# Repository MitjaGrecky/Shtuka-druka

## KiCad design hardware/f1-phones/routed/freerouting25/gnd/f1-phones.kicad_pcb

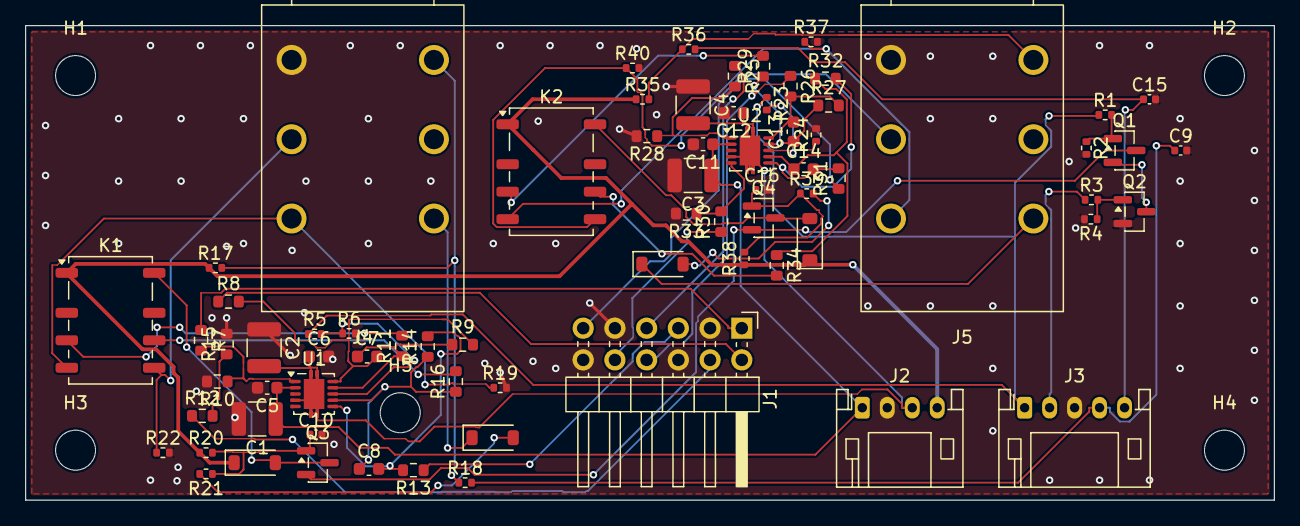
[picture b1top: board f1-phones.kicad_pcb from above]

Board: 2 copper layers, 100.0 x 38.0 mm, 78 parts (0 on the bottom side), 52 nets.

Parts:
C1, C2, C3, C4: 10u 25V; C_1210_3225Metric
C5, C6, C11, C12: 100n 25V; C_0603_1608Metric
C7, C8, C13, C14: 22p C0G; C_0603_1608Metric
C9, C10, C15, C16: 100n; C_0402_1005Metric
D1, D3: B5819W; D_SOD-123
D2, D4: 1N4148W; D_SOD-123
H1, H2, H3, H4, H5: M3; MountingHole_3.2mm_M3_ISO7380
J1: from A1; PinHeader_2x06_P2.54mm_Horizontal
J2: from PW; JST_PH_S4B-PH-K_1x04_P2.00mm_Horizontal
J3: from R1 (mute, detect); JST_PH_S5B-PH-K_1x05_P2.00mm_Horizontal
J4: PHONES 1; Jack_6.35mm_Cliff_S1_Horizontal
J5: PHONES 2; Jack_6.35mm_Cliff_S1_Horizontal
K1, K2: G6K-2F-Y 5V; Relay_DPDT_Omron_G6K-2F-Y
Q1, Q2, Q3, Q4: AO3400A; SOT-23
R1, R3, R5, R23: 1k; R_0402_1005Metric
R2, R4, R6, R17, R22, R24, R35, R40: 100k; R_0402_1005Metric
R7, R8, R12, R13, R25, R26, R30, R31: 10k; R_0603_1608Metric
R9, R10, R14, R15, R27, R28, R32, R33: 20k; R_0603_1608Metric
R11, R16, R29, R34: 10; R_0603_1608Metric
R18, R19, R36, R37: 10k; R_0402_1005Metric
R20, R38: 1M; R_0402_1005Metric
R21, R39: 100; R_0402_1005Metric
U1, U2: OPA1622; Texas_S-PVSON-N10

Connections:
+5V: D2.1, D4.1, J2.4, K1.A1, K2.A1, R17.1, R20.1, R35.1, R38.1
/+12V: C1.1, C3.1, C5.1, C11.1, J2.1, U1.2, U2.2
/-12V: C2.2, C4.2, C6.1, C12.1, J2.3, U1.4, U1.11, U2.4, U2.11
/COIL_K: Q1.3, Q3.2, Q4.2
/COIL_KS: Q1.2, Q2.3
/DET_HP1: C9.1, J3.4, R18.2
/DET_HP2: C15.1, J3.5, R36.2
/HP1L_IM: C7.2, R8.2, R9.2, U1.10
/HP1L_IP: R7.2, R10.1, U1.1
/HP1L_N: J1.2, R8.1
/HP1L_O: C7.1, R9.1, R11.1, U1.9
/HP1L_OR: K1.11, R11.2
/HP1L_P: J1.1, R7.1
/HP1R_IM: C8.2, R13.2, R14.2, U1.6
/HP1R_IP: R12.2, R15.1, U1.5
/HP1R_N: J1.5, R13.1
/HP1R_O: C8.1, R14.1, R16.1, U1.7
/HP1R_OR: K1.21, R16.2
/HP1R_P: J1.4, R12.1
/HP1_COIL: D2.2, K1.A2, Q3.3
/HP1_EN: R5.2, R6.1, U1.8
/HP1_G: C10.1, Q3.1, R20.2, R21.1
/HP1_GD: D1.2, R21.2
/HP1_RING: J4.R, K1.24, R22.1
/HP1_SN: J4.SN, R17.2, R18.1
/HP1_TIP: J4.T, K1.14, R19.1
/HP1_TN: D1.1, J4.TN
/HP2L_IM: C13.2, R26.2, R27.2, U2.10
/HP2L_IP: R25.2, R28.1, U2.1
/HP2L_N: J1.8, R26.1
/HP2L_O: C13.1, R27.1, R29.1, U2.9
/HP2L_OR: K2.11, R29.2
/HP2L_P: J1.7, R25.1
/HP2R_IM: C14.2, R31.2, R32.2, U2.6
/HP2R_IP: R30.2, R33.1, U2.5
/HP2R_N: J1.11, R31.1
/HP2R_O: C14.1, R32.1, R34.1, U2.7
/HP2R_OR: K2.21, R34.2
/HP2R_P: J1.10, R30.1
/HP2_COIL: D4.2, K2.A2, Q4.3
/HP2_EN: R23.2, R24.1, U2.8
/HP2_G: C16.1, Q4.1, R38.2, R39.1
/HP2_GD: D3.2, R39.2
/HP2_RING: J5.R, K2.24, R40.1
/HP2_SN: J5.SN, R35.2, R36.1
/HP2_TIP: J5.T, K2.14, R37.1
/HP2_TN: D3.1, J5.TN
/MUTE: J3.1, R1.1, R5.1, R23.1
/MUTE_G: Q1.1, R1.2, R2.1
/R2OK_G: Q2.1, R3.2, R4.1
/R2_OK: J3.2, R3.1
GND: C1.2, C2.1, C3.2, C4.1, C5.2, C6.2, C9.2, C10.2, C11.2, C12.2, C15.2, C16.2, J1.3, J1.6, J1.9, J1.12, J2.2, J3.3, J4.S, J5.S, Q2.2, R2.2, R4.2, R6.2, R10.2, R15.2, R19.2, R22.2, R24.2, R28.2, R33.2, R37.2, R40.2, U1.3, U2.3

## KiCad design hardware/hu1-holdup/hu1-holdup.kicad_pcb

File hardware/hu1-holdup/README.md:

# HU1 - hold-up module for the +-14 V rails (P129, P130)

**Status: rev 0.1 (21.11.2026): schematic and placed board, 2 layers, 35 x 45 mm, ERC 0, DRC 0, parity 0; not routed (UNROUTED rule: 4 capacitors, 2 resistors, 2 diodes, one 3-pin connector).**
Next to PW on a harness <= 80 mm (the place in the enclosure: designer, P130). On a loss of all power the +-14 V rails keep the audio boards alive for >= 6 ms until the output relays have opened (tasks/12, tasks/13 of the team folder).

| Block | Parts | Notes |
|---|---|---|
| Storage | 4 x 470 uF 25 V aluminium electrolytic 10 x 10.5 mm (2 per rail) | 0.94 mF per rail: 4.8 ms at 0.43 A, 7.1 ms at 0.29 A (with the Schottky drop) |
| Inrush limit | 2 x 10 ohm 1206 (one per rail) | LMR33640: soft start 4 ms, low-side limit 3.9-5 A, total output capacitance <= about 1000 uF: 1.4 A peak instead of 3.5 A |
| Discharge path | 2 x SS34 (C8678) | the storage feeds the rail when it sags; drop 0.3-0.4 V |
| Connector | Micro-Fit 3.0 1x3 vertical (43650-0315, latching) | 1 P14, 2 GND, 3 N14; PW has the same connector "to HU1" |

Parts to select (technologist): the 470 uF electrolytic (25 V, 105 C, 10 x 10.5), SS34 availability. License: CERN-OHL-S-2.0 (hardware), AGPL-3.0 (code).

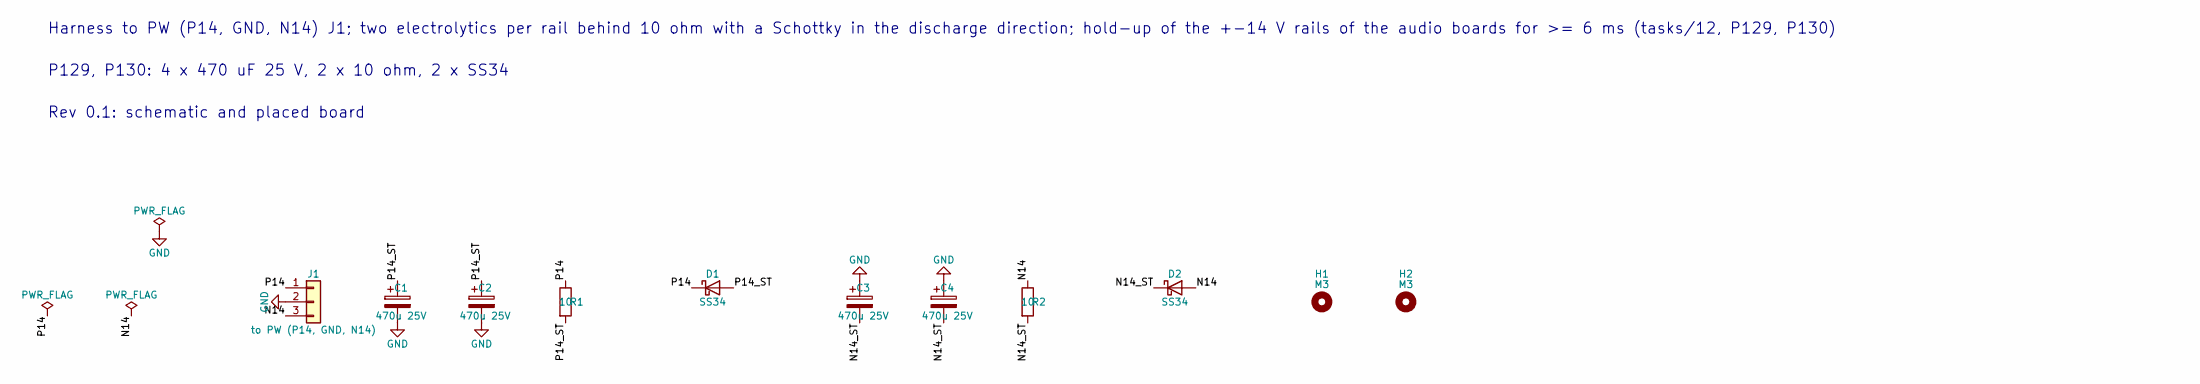
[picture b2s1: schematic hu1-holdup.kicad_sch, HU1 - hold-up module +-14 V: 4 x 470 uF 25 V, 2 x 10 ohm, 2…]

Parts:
C1, C2, C3, C4: 470u 25V; CP_Elec_10x10.5
D1, D2: SS34; D_SMA; LCSC C8678
H1, H2: M3; MountingHole_3.2mm_M3_ISO7380
J1: to PW (P14, GND, N14); Molex_Micro-Fit_3.0_43650-0315_1x03_P3.00mm_Vertical
R1, R2: 10; R_1206_3216Metric

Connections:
/N14: D2.2 (A), J1.3, R2.1
/N14_ST: C3.2, C4.2, D2.1 (K), R2.2
/P14: D1.1 (K), J1.1, R1.1
/P14_ST: C1.1, C2.1, D1.2 (A), R1.2
GND: C1.2, C2.2, C3.1, C4.1, J1.2

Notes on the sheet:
Harness to PW (P14, GND, N14) J1; two electrolytics per rail behind 10 ohm with a Schottky in the discharge direction; hold-up of the +-14 V rails of the audio boards for >= 6 ms (tasks/12, P129, P130)
P129, P130: 4 x 470 uF 25 V, 2 x 10 ohm, 2 x SS34
Rev 0.1: schematic and placed board

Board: 2 copper layers, 11 parts (0 on the bottom side), 5 nets, no tracks yet.

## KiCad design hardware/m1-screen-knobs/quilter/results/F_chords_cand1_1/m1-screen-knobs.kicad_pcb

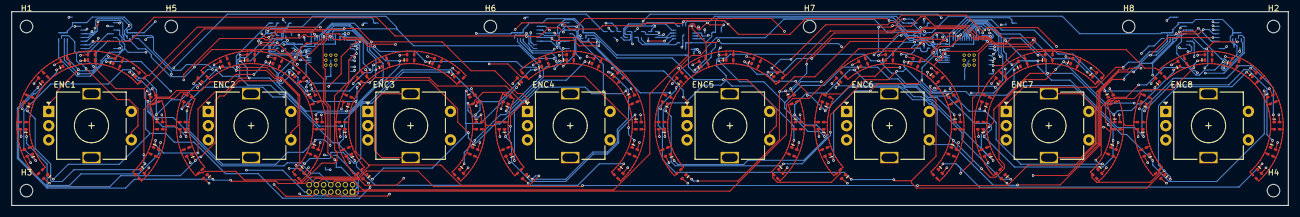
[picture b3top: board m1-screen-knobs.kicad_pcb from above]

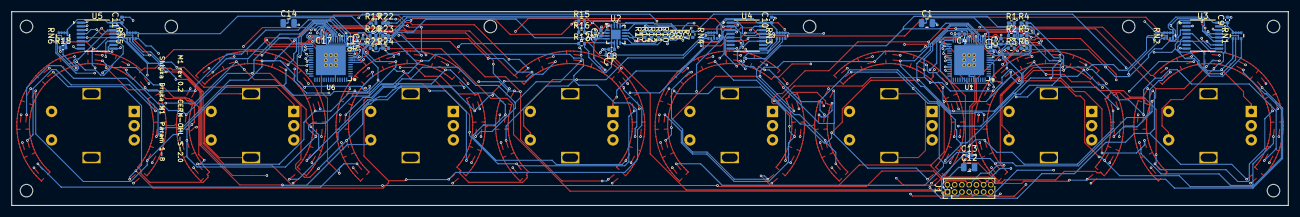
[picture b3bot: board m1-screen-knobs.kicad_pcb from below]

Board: 4 copper layers, 224.0 x 34.0 mm, 174 parts (54 on the bottom side), 114 nets.

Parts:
C1, C14: 4.7u; C_0805_2012Metric
C2, C7, C13, C15: 1u; C_0402_1005Metric
C3, C4, C6, C8, C9, C10, C11, C16, C17: 100n; C_0402_1005Metric
C5: 2.2n; C_0402_1005Metric
C12: 10u; C_0805_2012Metric
D1, D2, D3, D4, D5, D6, D7, D8, D9, D10, D11, D12, D13, D14, D15, D16, D17, D18, D19, D20, D21, D22, D23, D24, D25, D26, D27, D28, D29, D30, D31, D32, D33, D34, D35, D36, D37, D38, D39, D40, D41, D42, D43, D44, D45, D46, D47, D48, D49, D50, D51, D52, D53, D54, D55, D56, D57, D58, D59, D60, D61, D62, D63, D64, D65, D66, D67, D68, D69, D70, D71, D72, D73, D74, D75, D76, D77, D78, D79, D80, D81, D82, D83, D84, D85, D86, D87, D88, D89, D90, D91, D92, D93, D94, D95, D96, D97, D98, D99, D100, D101, D102, D103, D104: XL-1615RGBC-RF; LED_RGB_XL-1615RGBC_1.6x1.5mm
ENC1, ENC2, ENC3, ENC4, ENC5, ENC6, ENC7, ENC8: EC11E smooth, switch; RotaryEncoder_Alps_EC11E-Switch_Vertical_H20mm_Ring
H1, H2, H3, H4, H5, H6, H7, H8: M2; MountingHole_2.2mm_M2
J1: Module bus 2x7 1.27; PinHeader_2x07_P1.27mm_Vertical
R1, R19: 20k 1%; R_0402_1005Metric
R2, R17, R18, R20: 10k; R_0402_1005Metric
R3, R4, R5, R6, R21, R22, R23, R24: 0; R_0402_1005Metric
R7, R8, R9, R10, R11, R12, R13, R14: 560; R_0402_1005Metric
R15, R16: 4.7k; R_0402_1005Metric
RN1, RN2, RN3, RN4, RN5, RN6: 4x10k; R_Array_Convex_4x0402
U1, U6: IS31FL3741A-QFLS4-TR; QFN-60-1EP_7x7mm_P0.4mm_EP5.25x5.25mm
U2: CY8CMBR3108-LQXIT; QFN-16-1EP_3x3mm_P0.5mm_EP1.7x1.7mm
U3, U4, U5: 74HC165PW; TSSOP-16_4.4x5mm_P0.65mm

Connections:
+3V3: C7.1, C8.1, C9.1, C10.1, C11.1, C13.1, J1.5, R2.2, R15.2, R16.2, R17.2, R18.2, R20.2, RN1.5, RN1.6, RN1.7, RN1.8, RN2.5, RN2.6, RN2.7, RN2.8, RN3.5, RN3.6, RN3.7, RN3.8, RN4.5, RN4.6, RN4.7, RN4.8, RN5.5, RN5.6, RN5.7, RN5.8, RN6.5, RN6.6, RN6.7, RN6.8, U2.5, U2.6, U3.16, U4.16, U5.16
+5V: C1.1, C2.1, C3.1, C4.1, C12.1, C14.1, C15.1, C16.1, C17.1, J1.1, J1.2, R6.2, R24.2, U1.14, U1.15, U1.25, U6.14, U6.15, U6.25
A_ADDR: R3.1, R4.1, R5.1, R6.1, U1.8
A_CS1: D1.1, D2.1, D3.1, D4.1, D5.1, D6.1, D7.1, D8.1, D9.1, U1.26
A_CS2: D1.3, D2.3, D3.3, D4.3, D5.3, D6.3, D7.3, D8.3, D9.3, U1.27
A_CS3: D1.4, D2.4, D3.4, D4.4, D5.4, D6.4, D7.4, D8.4, D9.4, U1.28
A_CS4: D18.1, D19.1, D20.1, D21.1, D22.1, D23.1, D24.1, D25.1, D26.1, U1.29
A_CS5: D18.3, D19.3, D20.3, D21.3, D22.3, D23.3, D24.3, D25.3, D26.3, U1.30
A_CS6: D18.4, D19.4, D20.4, D21.4, D22.4, D23.4, D24.4, D25.4, D26.4, U1.31
A_CS7: D10.1, D11.1, D12.1, D13.1, D14.1, D15.1, D16.1, D17.1, U1.32
A_CS8: D10.3, D11.3, D12.3, D13.3, D14.3, D15.3, D16.3, D17.3, U1.33
A_CS9: D10.4, D11.4, D12.4, D13.4, D14.4, D15.4, D16.4, D17.4, U1.34
A_CS10: D27.1, D28.1, D29.1, D30.1, D31.1, D32.1, D33.1, D34.1, D35.1, U1.35
A_CS11: D27.3, D28.3, D29.3, D30.3, D31.3, D32.3, D33.3, D34.3, D35.3, U1.37
A_CS12: D27.4, D28.4, D29.4, D30.4, D31.4, D32.4, D33.4, D34.4, D35.4, U1.38
A_CS13: D44.1, D45.1, D46.1, D47.1, D48.1, D49.1, D50.1, D51.1, D52.1, U1.39
A_CS14: D44.3, D45.3, D46.3, D47.3, D48.3, D49.3, D50.3, D51.3, D52.3, U1.40
A_CS15: D44.4, D45.4, D46.4, D47.4, D48.4, D49.4, D50.4, D51.4, D52.4, U1.41
A_CS16: D36.1, D37.1, D38.1, D39.1, D40.1, D41.1, D42.1, D43.1, U1.42
A_CS17: D36.3, D37.3, D38.3, D39.3, D40.3, D41.3, D42.3, D43.3, U1.43
A_CS18: D36.4, D37.4, D38.4, D39.4, D40.4, D41.4, D42.4, D43.4, U1.44
A_REXT: R1.1, U1.13
A_SDB: R2.1, U1.11
A_SW1: D1.2, D10.2, D18.2, D27.2, D36.2, D44.2, U1.16
A_SW2: D2.2, D11.2, D19.2, D28.2, D37.2, D45.2, U1.17
A_SW3: D3.2, D12.2, D20.2, D29.2, D38.2, D46.2, U1.18
A_SW4: D4.2, D13.2, D21.2, D30.2, D39.2, D47.2, U1.19
A_SW5: D5.2, D14.2, D22.2, D31.2, D40.2, D48.2, U1.20
A_SW6: D6.2, D15.2, D23.2, D32.2, D41.2, D49.2, U1.21
A_SW7: D7.2, D16.2, D24.2, D33.2, D42.2, D50.2, U1.22
A_SW8: D8.2, D17.2, D25.2, D34.2, D43.2, D51.2, U1.23
A_SW9: D9.2, D26.2, D35.2, D52.2, U1.24
B_ADDR: R21.1, R22.1, R23.1, R24.1, U6.8
B_CS1: D53.1, D54.1, D55.1, D56.1, D57.1, D58.1, D59.1, D60.1, D61.1, U6.26
B_CS2: D53.3, D54.3, D55.3, D56.3, D57.3, D58.3, D59.3, D60.3, D61.3, U6.27
B_CS3: D53.4, D54.4, D55.4, D56.4, D57.4, D58.4, D59.4, D60.4, D61.4, U6.28
B_CS4: D70.1, D71.1, D72.1, D73.1, D74.1, D75.1, D76.1, D77.1, D78.1, U6.29
B_CS5: D70.3, D71.3, D72.3, D73.3, D74.3, D75.3, D76.3, D77.3, D78.3, U6.30
B_CS6: D70.4, D71.4, D72.4, D73.4, D74.4, D75.4, D76.4, D77.4, D78.4, U6.31
B_CS7: D62.1, D63.1, D64.1, D65.1, D66.1, D67.1, D68.1, D69.1, U6.32
B_CS8: D62.3, D63.3, D64.3, D65.3, D66.3, D67.3, D68.3, D69.3, U6.33
B_CS9: D62.4, D63.4, D64.4, D65.4, D66.4, D67.4, D68.4, D69.4, U6.34
B_CS10: D79.1, D80.1, D81.1, D82.1, D83.1, D84.1, D85.1, D86.1, D87.1, U6.35
B_CS11: D79.3, D80.3, D81.3, D82.3, D83.3, D84.3, D85.3, D86.3, D87.3, U6.37
B_CS12: D79.4, D80.4, D81.4, D82.4, D83.4, D84.4, D85.4, D86.4, D87.4, U6.38
B_CS13: D96.1, D97.1, D98.1, D99.1, D100.1, D101.1, D102.1, D103.1, D104.1, U6.39
B_CS14: D96.3, D97.3, D98.3, D99.3, D100.3, D101.3, D102.3, D103.3, D104.3, U6.40
B_CS15: D96.4, D97.4, D98.4, D99.4, D100.4, D101.4, D102.4, D103.4, D104.4, U6.41
B_CS16: D88.1, D89.1, D90.1, D91.1, D92.1, D93.1, D94.1, D95.1, U6.42
B_CS17: D88.3, D89.3, D90.3, D91.3, D92.3, D93.3, D94.3, D95.3, U6.43
B_CS18: D88.4, D89.4, D90.4, D91.4, D92.4, D93.4, D94.4, D95.4, U6.44
B_REXT: R19.1, U6.13
B_SDB: R20.1, U6.11
B_SW1: D53.2, D62.2, D70.2, D79.2, D88.2, D96.2, U6.16
B_SW2: D54.2, D63.2, D71.2, D80.2, D89.2, D97.2, U6.17
B_SW3: D55.2, D64.2, D72.2, D81.2, D90.2, D98.2, U6.18
B_SW4: D56.2, D65.2, D73.2, D82.2, D91.2, D99.2, U6.19
B_SW5: D57.2, D66.2, D74.2, D83.2, D92.2, D100.2, U6.20
B_SW6: D58.2, D67.2, D75.2, D84.2, D93.2, D101.2, U6.21
B_SW7: D59.2, D68.2, D76.2, D85.2, D94.2, D102.2, U6.22
B_SW8: D60.2, D69.2, D77.2, D86.2, D95.2, D103.2, U6.23
B_SW9: D61.2, D78.2, D87.2, D104.2, U6.24
CMOD: C5.1, U2.3
E0_A: ENC1.A, RN1.1, U3.6
E0_B: ENC1.B, RN1.2, U3.5
E0_SW: ENC1.S1, RN1.3, U3.4
E1_A: ENC2.A, RN1.4, U3.3
E1_B: ENC2.B, RN2.1, U3.14
E1_SW: ENC2.S1, RN2.2, U3.13
E2_A: ENC3.A, RN2.3, U3.12
E2_B: ENC3.B, RN2.4, U3.11
E2_SW: ENC3.S1, RN3.1, U4.6
E3_A: ENC4.A, RN3.2, U4.5
E3_B: ENC4.B, RN3.3, U4.4
E3_SW: ENC4.S1, RN3.4, U4.3
E4_A: ENC5.A, RN4.1, U4.14
E4_B: ENC5.B, RN4.2, U4.13
E4_SW: ENC5.S1, RN4.3, U4.12
E5_A: ENC6.A, RN4.4, U4.11
E5_B: ENC6.B, RN5.1, U5.6
E5_SW: ENC6.S1, RN5.2, U5.5
E6_A: ENC7.A, RN5.3, U5.4
E6_B: ENC7.B, RN5.4, U5.3
E6_SW: ENC7.S1, RN6.1, U5.14
E7_A: ENC8.A, RN6.2, U5.13
E7_B: ENC8.B, RN6.3, U5.12
E7_SW: ENC8.S1, RN6.4, U5.11
GND: C1.2, C2.2, C3.2, C4.2, C5.2, C6.2, C7.2, C8.2, C9.2, C10.2, C11.2, C12.2, C13.2, C14.2, C15.2, C16.2, C17.2, ENC1.C, ENC1.S2, ENC2.C, ENC2.S2, ENC3.C, ENC3.S2, ENC4.C, ENC4.S2, ENC5.C, ENC5.S2, ENC6.C, ENC6.S2, ENC7.C, ENC7.S2, ENC8.C, ENC8.S2, J1.3, J1.4, J1.6, J1.10, R1.2, R3.2, R19.2, R21.2, U1.12, U1.36, U1.55, U1.61, U2.7, U2.17, U3.8, U3.15, U4.8, U4.15, U5.8, U5.15, U6.12, U6.36, U6.55, U6.61
SCL: J1.8, R4.2, R16.1, R22.2, U1.10, U2.15, U6.10
SDA: J1.7, R5.2, R15.1, R23.2, U1.9, U2.14, U6.9
SR_CLK: J1.12, U3.2, U4.2, U5.2
SR_IN: J1.14, R18.1, U5.10
SR_OUT: J1.13, U3.9
SR_Q3: U3.10, U4.9
SR_Q4: U4.10, U5.9
TOUCH0: ENC1.MP, R7.2
TOUCH1: ENC2.MP, R8.2
TOUCH2: ENC3.MP, R9.2
TOUCH3: ENC4.MP, R10.2
TOUCH4: ENC5.MP, R11.2
TOUCH5: ENC6.MP, R12.2
TOUCH6: ENC7.MP, R13.2
TOUCH7: ENC8.MP, R14.2
TR0: R7.1, U2.1
TR1: R8.1, U2.2
TR2: R9.1, U2.12
TR3: R10.1, U2.13
TR4: R11.1, U2.8
TR5: R12.1, U2.9
TR6: R13.1, U2.10
TR7: R14.1, U2.11
VREG: C6.1, U2.4
~INT: J1.9, R17.1, U1.7, U2.16, U6.7
~SR_LOAD: J1.11, U3.1, U4.1, U5.1

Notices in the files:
hardware/f1-phones/routed/freerouting25/gnd/f1-phones.kicad_pcb:
Shtuka Druka - open hardware, CERN-OHL-S-2.0
Shtuka Druka CERN-OHL-S-2.0
hardware/m1-screen-knobs/quilter/results/F_chords_cand1_1/m1-screen-knobs.kicad_pcb:
M1 rev 0.2  CERN-OHL-S-2.0
